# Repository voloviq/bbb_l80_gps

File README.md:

# bbb_l80_gps
bbb cape with L80 GPS

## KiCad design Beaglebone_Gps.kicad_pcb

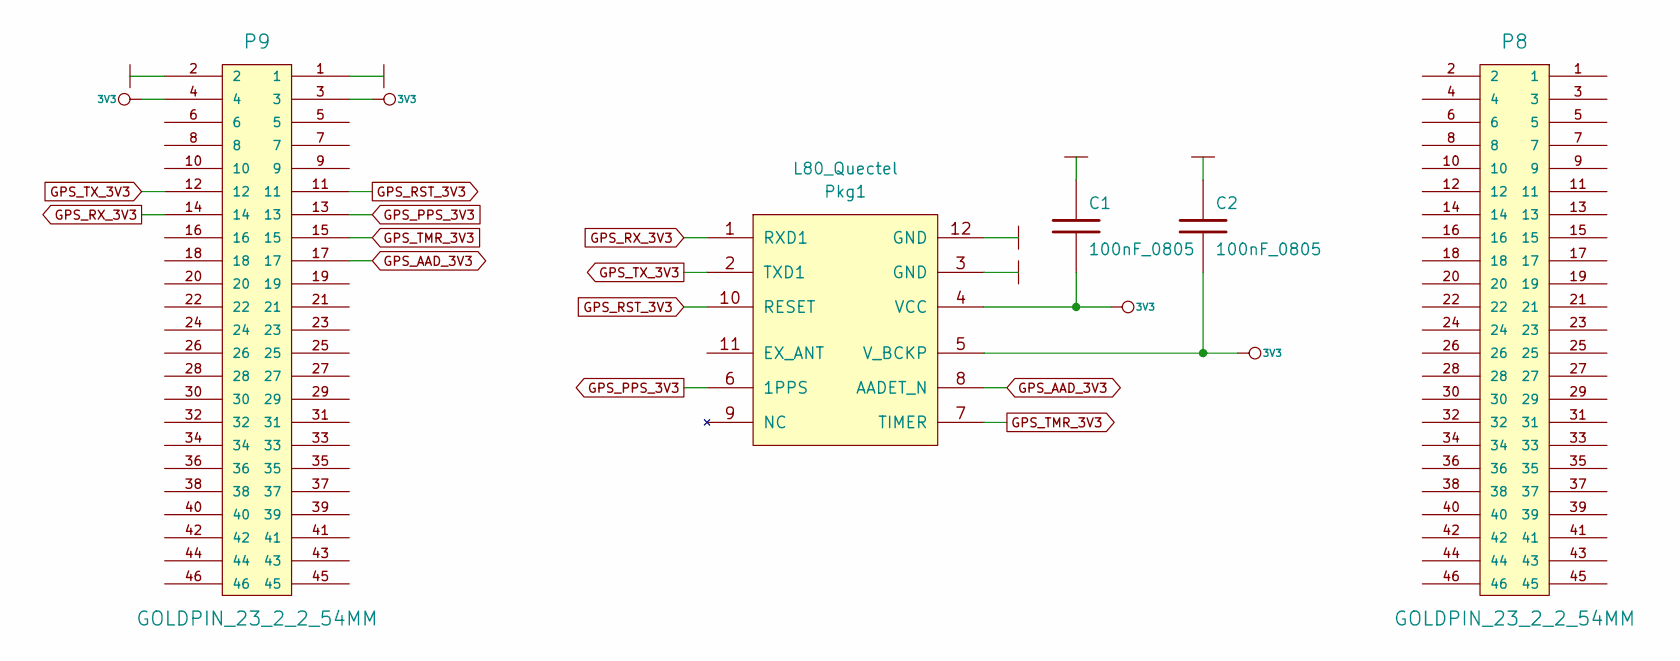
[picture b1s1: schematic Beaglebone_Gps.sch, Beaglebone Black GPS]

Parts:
C1, C2: 100nF_0805
P8, P9: GOLDPIN_23_2_2_54MM; Goldpin_23_2_2_54mm_SMT
Pkg1: L80_Quectel

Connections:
3V3: C1.2, C2.2, P9.3, P9.4, Pkg1.4 (VCC), Pkg1.5 (V_BCKP)
GND: C1.1, C2.1, P9.1, P9.2, Pkg1.3 (GND), Pkg1.12 (GND)
GPS_AAD_3V3: P9.17, Pkg1.8 (AADET_N)
GPS_PPS_3V3: P9.13, Pkg1.6 (1PPS)
GPS_RST_3V3: P9.11, Pkg1.10 (RESET)
GPS_RX_3V3: P9.14, Pkg1.1 (RXD1)
GPS_TMR_3V3: P9.15, Pkg1.7 (TIMER)
GPS_TX_3V3: P9.12, Pkg1.2 (TXD1)

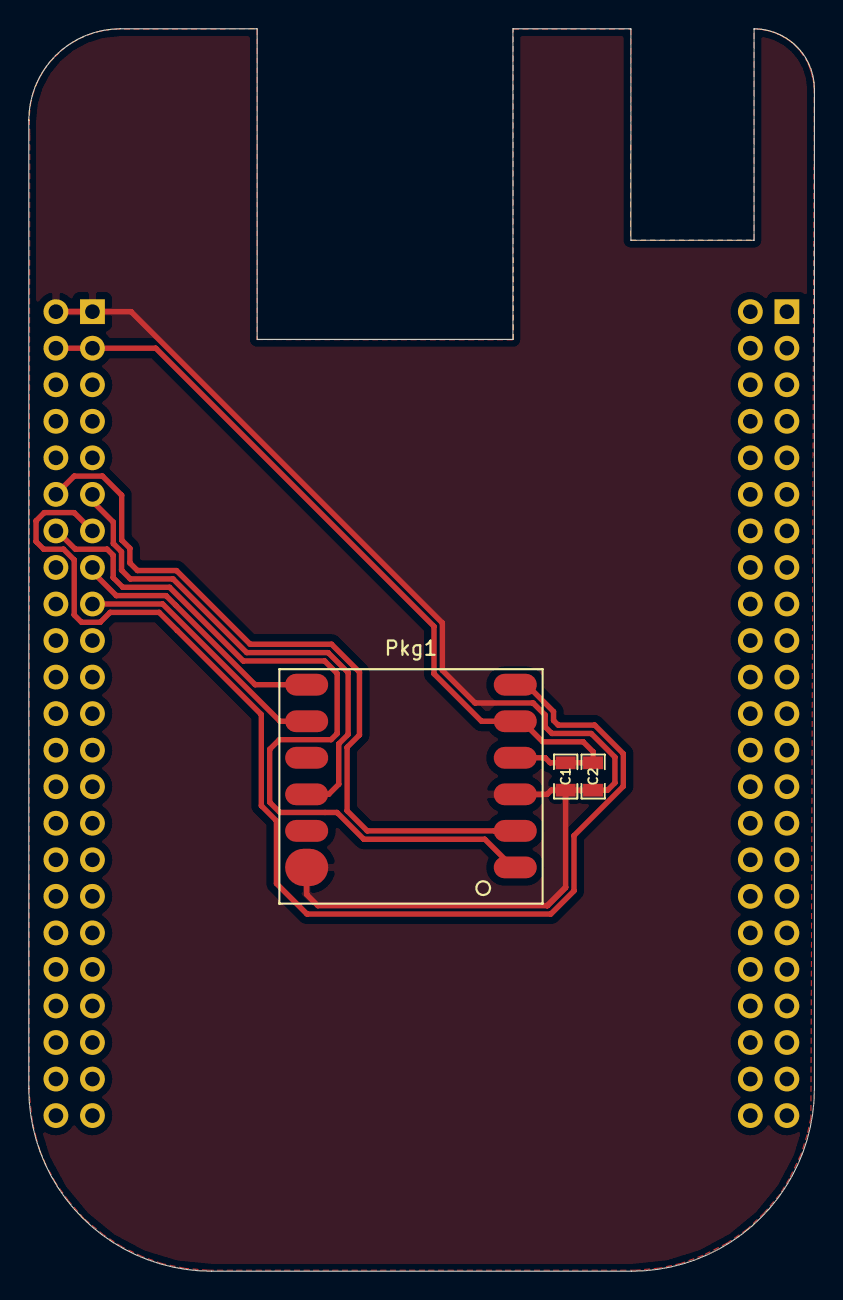
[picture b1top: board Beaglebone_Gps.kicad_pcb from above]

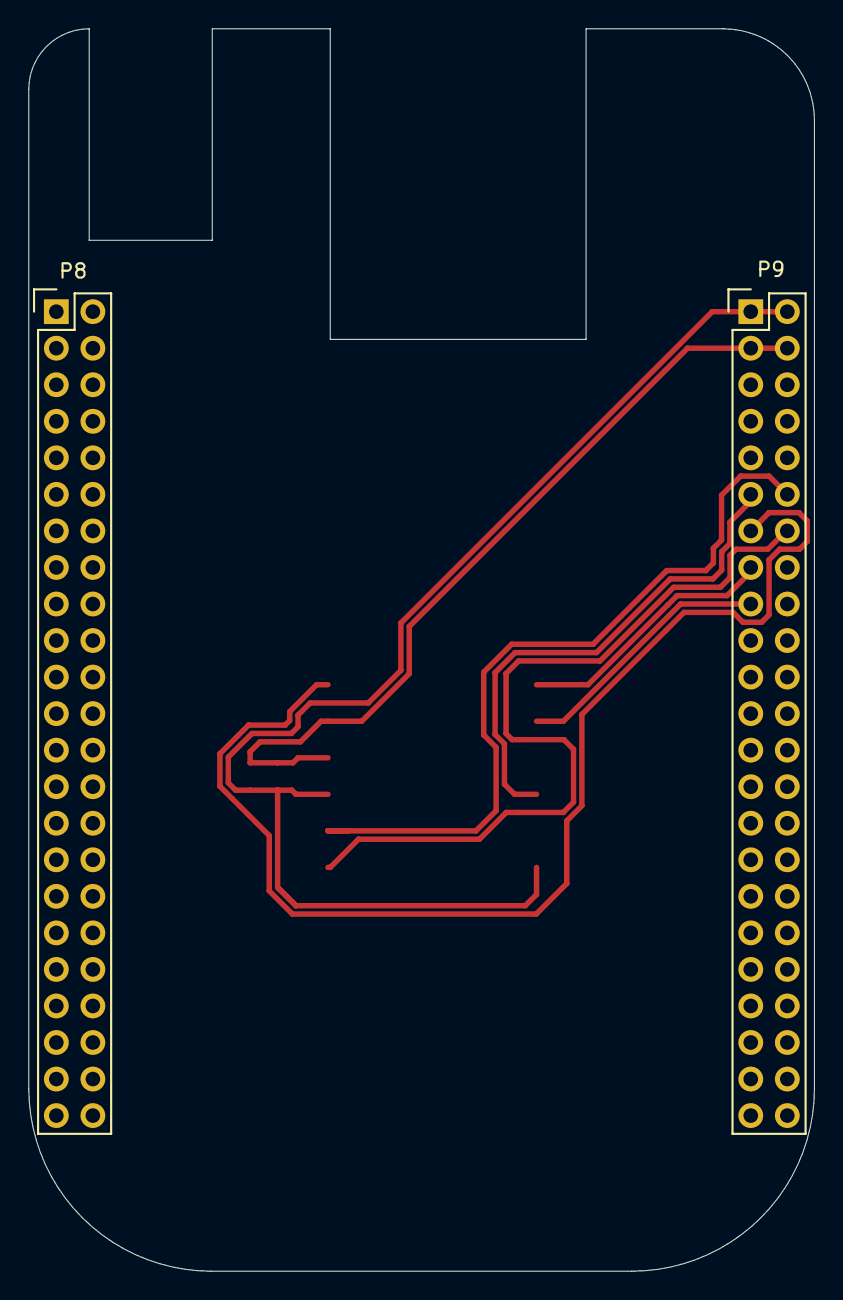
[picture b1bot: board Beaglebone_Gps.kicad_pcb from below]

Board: 2 copper layers, 54.6 x 86.4 mm, 5 parts (2 on the bottom side), 8 nets.

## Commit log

2017-10-24 Initial
2017-10-24 Corrected GPS 3d model
